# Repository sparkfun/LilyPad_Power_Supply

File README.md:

LilyPad Power Supply
========================================

[*LilyPad Power Supply (DEV-11259)*](https://www.sparkfun.com/products/11259)

A small, but mighty power supply. This board was designed to be as small and inconspicuous as possible. 
Pop in a AAA battery, flip the power switch, and you will have a 5V supply to power your LilyPad circuit. 
Good up to 200mA. Short circuit protected.

Repository Contents
-------------------
 
* **/Hardware** - Eagle design files (.brd, .sch)
* **/Production** - Production panel files (.brd)

Documentation
--------------
* **[SparkFun Fritzing repo](https://github.com/sparkfun/Fritzing_Parts)** - Fritzing diagrams for SparkFun products.
* **[SparkFun 3D Model repo](https://github.com/sparkfun/3D_Models)** - 3D models of SparkFun products. 

License Information
-------------------
This product is _**open source**_! 

The **hardware** is released under [Creative Commons ShareAlike 4.0 International](https://creativecommons.org/licenses/by-sa/4.0/).

Please use, reuse, and modify these files as you see fit. Please maintain attribution to SparkFun Electronics and release anything derivative under the same license.

Distributed as-is; no warranty is given.

- Your friends at SparkFun.

_**Note:** A portion of this sale is given back to Dr. Leah Buechley for continued development and education of e-textiles._

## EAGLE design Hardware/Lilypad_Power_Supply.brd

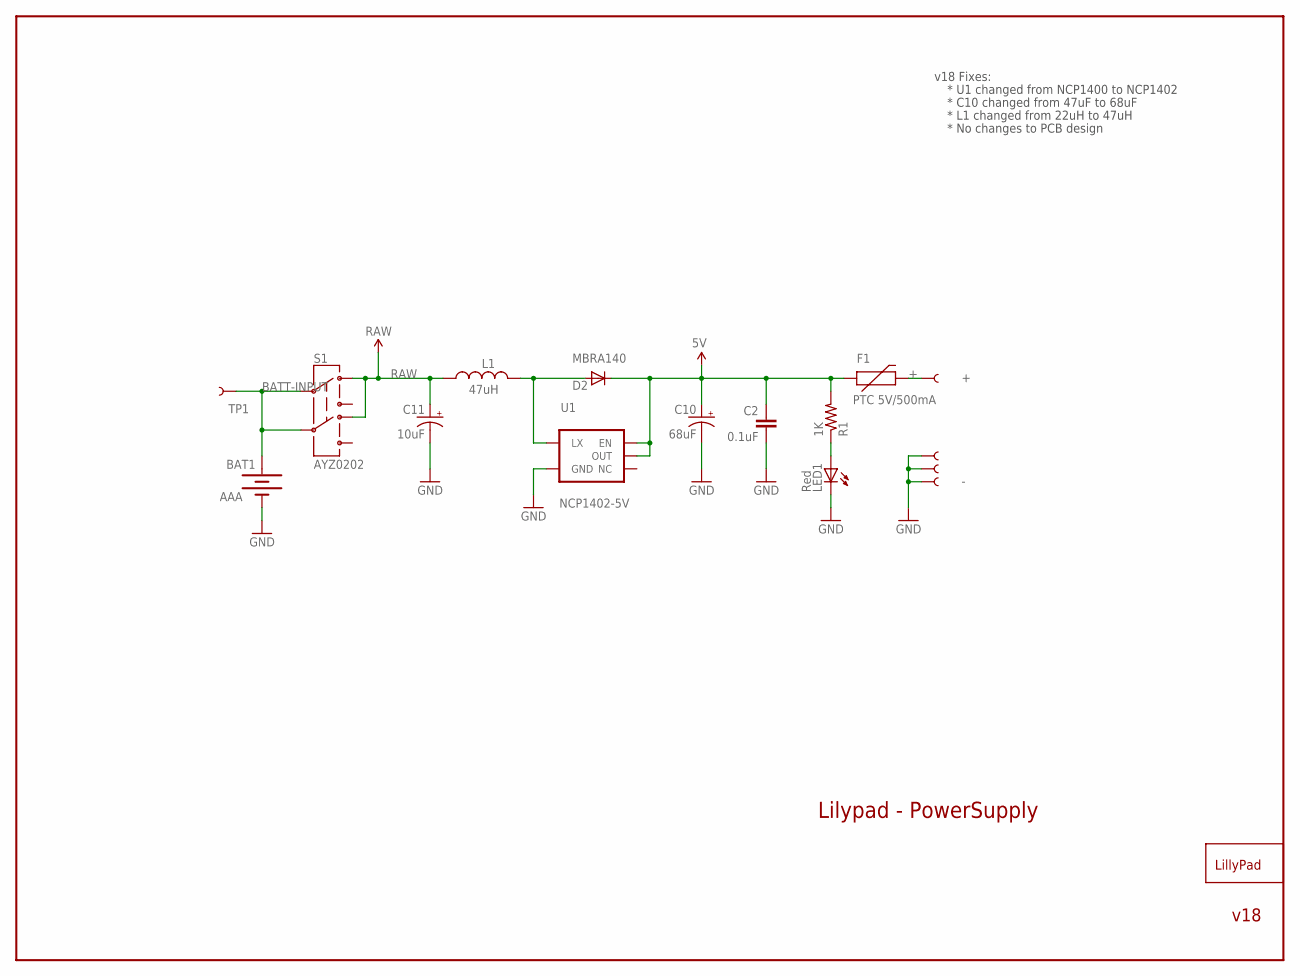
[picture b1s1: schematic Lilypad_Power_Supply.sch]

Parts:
BAT1: AAA; BATTERY-AAA
C2: 0.1uF; 0603-CAP
C10: 68uF; EIA3528-21
C11: 10uF; CPOL_1206
D2: MBRA140; SMA-DIODE
F1: PTC 5V/500mA; PTC-1206
L1: 47uH; CR54
LED1: Red; LED-1206
R1: 1K; 0603-RES
S1: AYZ0202
TP1: TEST-POINT3X5; PAD.03X.05
U1: NCP1402-5V; SOT23-5
U$1, U$2, U$4, U$5: SEWTAP10; PETAL-LONG-2-2SIDE
U$7: LOGO-LPLP; LOGO-LILYPAD

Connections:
5V: C2.1, C10.A (+), D2.C, F1.1, R1.2, U1.1 (EN), U1.2 (OUT)
+: F1.2, U$1.1
BATT-INPUT: BAT1.PWR@1 (+), S1.2, S1.5, TP1.P$1
GND: BAT1.GND@1 (-), C2.2, C10.C (-), C11.C (-), LED1.C, U1.4 (GND), U$2.1, U$4.1, U$5.1
unnamed: LED1.A, R1.1
unnamed: D2.A, L1.P$1 (1), U1.5 (LX)
RAW: C11.A (+), L1.P$2 (2), S1.3 (1), S1.6 (4)

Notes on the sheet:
Lilypad - PowerSupply
v18
v18 Fixes:
* U1 changed from NCP1400 to NCP1402
* C10 changed from 47uF to 68uF
* L1 changed from 22uH to 47uH
* No changes to PCB design

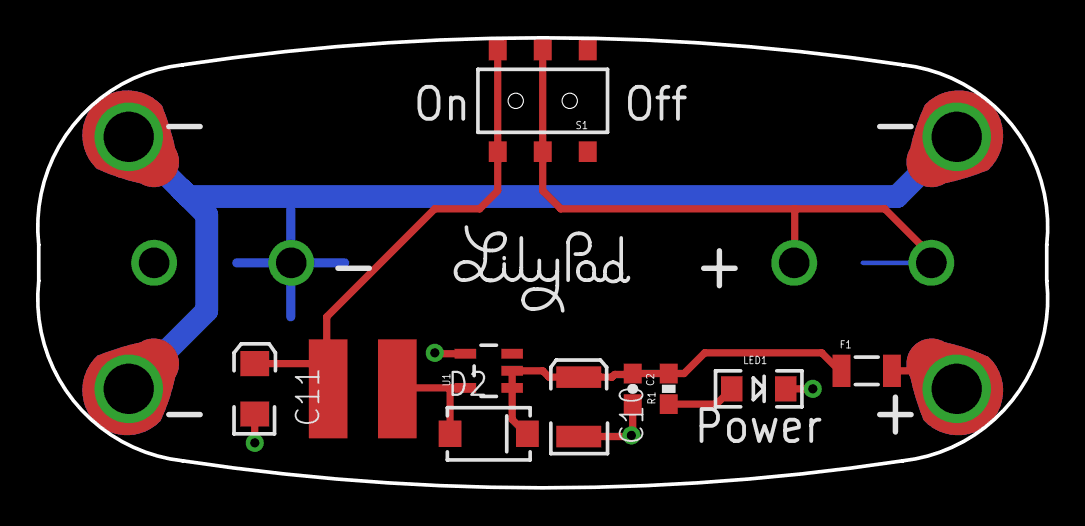
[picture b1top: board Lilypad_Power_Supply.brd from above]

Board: 2 copper layers, 56.1 x 25.0 mm, 17 parts (1 on the bottom side), 7 nets.

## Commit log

2015-05-05 Adding hardware files, updating README
